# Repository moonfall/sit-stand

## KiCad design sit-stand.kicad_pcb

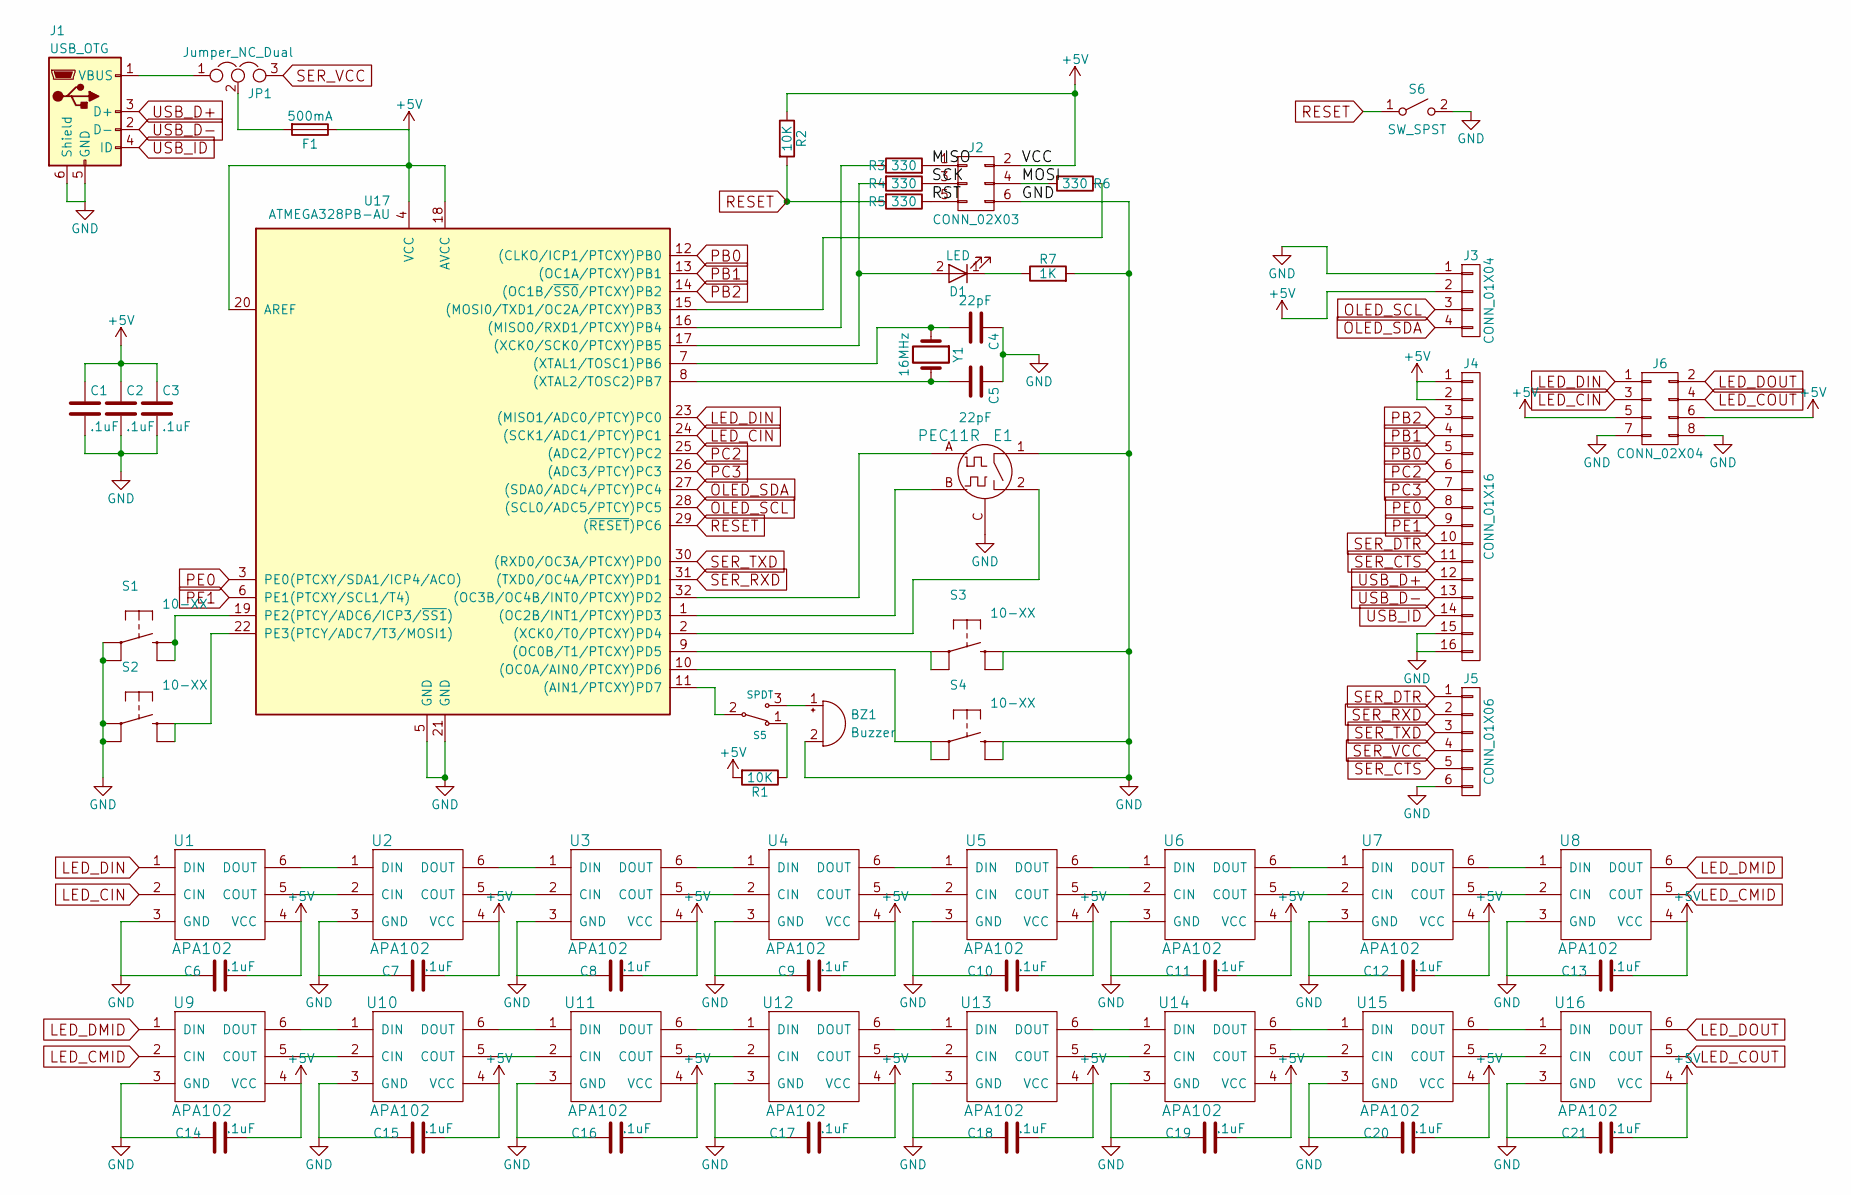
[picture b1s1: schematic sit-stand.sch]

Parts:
BZ1: Buzzer; BUZZER
C1, C2, C3, C6, C7, C8, C9, C10, C11, C12, C13, C14, C15, C16, C17, C18, C19, C20, C21: .1uF; C_0805_HandSoldering
C4, C5: 22pF; C_0805_HandSoldering
D1: LED; LED_0805
E1: PEC11R; pec11r
F1: 500mA; Fuse_SMD1206_HandSoldering
J1: USB_OTG; USB_Micro-B
J2: CONN_02X03; Pin_Header_Straight_2x03_Pitch2.54mm
J3: CONN_01X04; Pin_Header_Straight_1x04_Pitch2.54mm
J4: CONN_01X16; Pin_Header_Straight_1x16_Pitch2.54mm
J5: CONN_01X06; Pin_Header_Straight_1x06_Pitch2.54mm
J6: CONN_02X04; Pin_Header_Straight_2x04_Pitch2.54mm
JP1: Jumper_NC_Dual; Pin_Header_Straight_1x03_Pitch2.54mm
R1, R2: 10K; R_0805_HandSoldering
R3, R4, R5, R6: 330; R_0805_HandSoldering
R7: 1K; R_0805_HandSoldering
S1, S2, S3, S4: 10-XX; SW_TH_Tactile_Omron_B3F-10xx
S5: SPDT; SW_SPDT_CK-JS102011SAQN
S6: SW_SPST; SW_SPST_PTS645
U1, U2, U3, U4, U5, U6, U7, U8, U9, U10, U11, U12, U13, U14, U15, U16: APA102
U17: ATMEGA328PB-AU; TQFP-32_7x7mm_Pitch0.8mm
Y1: 16MHz; Crystal_HC49-U_Vertical

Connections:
+5V: C1.1, C2.1, C3.1, C6.2, C7.2, C8.2, C9.2, C10.2, C11.2, C12.2, C13.2, C14.2, C15.2, C16.2, C17.2, C18.2, C19.2, C20.2, C21.2, F1.1, J2.2, J3.2, J4.1, J4.2, J6.5, J6.6, R1.2, R2.1, U1.4 (VCC), U2.4 (VCC), U3.4 (VCC), U4.4 (VCC), U5.4 (VCC), U6.4 (VCC), U7.4 (VCC), U8.4 (VCC), U9.4 (VCC), U10.4 (VCC), U11.4 (VCC), U12.4 (VCC), U13.4 (VCC), U14.4 (VCC), U15.4 (VCC), U16.4 (VCC), U17.4 (VCC), U17.18 (AVCC), U17.20 (AREF)
/MISO: J2.1, R3.2
/MOSI: J2.4, R6.2
/RST: J2.5, R5.1
/SCK: J2.3, R4.1
GND: BZ1.2 (+), C1.2, C2.2, C3.2, C4.1, C5.1, C6.1, C7.1, C8.1, C9.1, C10.1, C11.1, C12.1, C13.1, C14.1, C15.1, C16.1, C17.1, C18.1, C19.1, C20.1, C21.1, E1.1, E1.C, J1.5 (GND), J1.6 (Shield), J2.6, J3.1, J4.15, J4.16, J5.6, J6.7, J6.8, R7.2, S1.3, S1.4 (P1), S2.3, S2.4 (P1), S3.1 (S), S3.2 (S1), S4.1 (S), S4.2 (S1), S6.2 (B), U1.3 (GND), U2.3 (GND), U3.3 (GND), U4.3 (GND), U5.3 (GND), U6.3 (GND), U7.3 (GND), U8.3 (GND), U9.3 (GND), U10.3 (GND), U11.3 (GND), U12.3 (GND), U13.3 (GND), U14.3 (GND), U15.3 (GND), U16.3 (GND), U17.5 (GND), U17.21 (GND)
LED_CIN: J6.3, U1.2 (CIN), U17.24 ((SCK1/ADC1/PTCY)PC1)
LED_CMID: U8.5 (COUT), U9.2 (CIN)
LED_COUT: J6.4, U16.5 (COUT)
LED_DIN: J6.1, U1.1 (DIN), U17.23 ((MISO1/ADC0/PTCY)PC0)
LED_DMID: U8.6 (DOUT), U9.1 (DIN)
LED_DOUT: J6.2, U16.6 (DOUT)
unnamed: BZ1.1 (-), S5.3
unnamed: C4.2, U17.7 ((XTAL1/TOSC1)PB6), Y1.1
unnamed: C5.2, U17.8 ((XTAL2/TOSC2)PB7), Y1.2
unnamed: D1.1 (K), R7.1
unnamed: D1.2 (A), R4.2, U17.17 ((XCK0/SCK0/PTCXY)PB5)
unnamed: E1.2, U17.2 ((XCK0/T0/PTCXY)PD4)
unnamed: E1.A, U17.32 ((OC3B/OC4B/INT0/PTCXY)PD2)
unnamed: E1.B, U17.1 ((OC2B/INT1/PTCXY)PD3)
unnamed: F1.2, JP1.2
unnamed: J1.1 (VBUS), JP1.1
unnamed: R1.1, S5.1
unnamed: R3.1, U17.16 ((MISO0/RXD1/PTCXY)PB4)
unnamed: R6.1, U17.15 ((MOSI0/TXD1/OC2A/PTCXY)PB3)
unnamed: S1.1 (S), S1.2 (S1), U17.19 (PE2(PTCY/ADC6/ICP3/~SS1~))
unnamed: S2.1 (S), S2.2 (S1), U17.22 (PE3(PTCY/ADC7/T3/MOSI1))
unnamed: S3.3, S3.4 (P1), U17.9 ((OC0B/T1/PTCXY)PD5)
unnamed: S4.3, S4.4 (P1), U17.10 ((OC0A/AIN0/PTCXY)PD6)
unnamed: S5.2, U17.11 ((AIN1/PTCXY)PD7)
unnamed: U1.5 (COUT), U2.2 (CIN)
unnamed: U1.6 (DOUT), U2.1 (DIN)
unnamed: U2.5 (COUT), U3.2 (CIN)
unnamed: U2.6 (DOUT), U3.1 (DIN)
unnamed: U3.5 (COUT), U4.2 (CIN)
unnamed: U3.6 (DOUT), U4.1 (DIN)
unnamed: U4.5 (COUT), U5.2 (CIN)
unnamed: U4.6 (DOUT), U5.1 (DIN)
unnamed: U5.5 (COUT), U6.2 (CIN)
unnamed: U5.6 (DOUT), U6.1 (DIN)
unnamed: U6.5 (COUT), U7.2 (CIN)
unnamed: U6.6 (DOUT), U7.1 (DIN)
unnamed: U7.5 (COUT), U8.2 (CIN)
unnamed: U7.6 (DOUT), U8.1 (DIN)
unnamed: U9.6 (DOUT), U10.1 (DIN)
unnamed: U9.5 (COUT), U10.2 (CIN)
unnamed: U10.5 (COUT), U11.2 (CIN)
unnamed: U10.6 (DOUT), U11.1 (DIN)
unnamed: U11.5 (COUT), U12.2 (CIN)
unnamed: U11.6 (DOUT), U12.1 (DIN)
unnamed: U12.5 (COUT), U13.2 (CIN)
unnamed: U12.6 (DOUT), U13.1 (DIN)
unnamed: U13.5 (COUT), U14.2 (CIN)
unnamed: U13.6 (DOUT), U14.1 (DIN)
unnamed: U14.5 (COUT), U15.2 (CIN)
unnamed: U14.6 (DOUT), U15.1 (DIN)
unnamed: U15.5 (COUT), U16.2 (CIN)
unnamed: U15.6 (DOUT), U16.1 (DIN)
OLED_SCL: J3.3, U17.28 ((SCL0/ADC5/PTCY)PC5)
OLED_SDA: J3.4, U17.27 ((SDA0/ADC4/PTCY)PC4)
PB0: J4.5, U17.12 ((CLKO/ICP1/PTCXY)PB0)
PB1: J4.4, U17.13 ((OC1A/PTCXY)PB1)
PB2: J4.3, U17.14 ((OC1B/~SS0~/PTCXY)PB2)
PC2: J4.6, U17.25 ((ADC2/PTCY)PC2)
PC3: J4.7, U17.26 ((ADC3/PTCY)PC3)
PE0: J4.8, U17.3 (PE0(PTCXY/SDA1/ICP4/ACO))
PE1: J4.9, U17.6 (PE1(PTCXY/SCL1/T4))
RESET: R2.2, R5.2, S6.1 (A), U17.29 ((~RESET~)PC6)
SER_CTS: J4.11, J5.5
SER_DTR: J4.10, J5.1
SER_RXD: J5.2, U17.31 ((TXD0/OC4A/PTCXY)PD1)
SER_TXD: J5.3, U17.30 ((RXD0/OC3A/PTCXY)PD0)
SER_VCC: J5.4, JP1.3
USB_D+: J1.3 (D+), J4.12
USB_D-: J1.2 (D-), J4.13
USB_ID: J1.4 (ID), J4.14

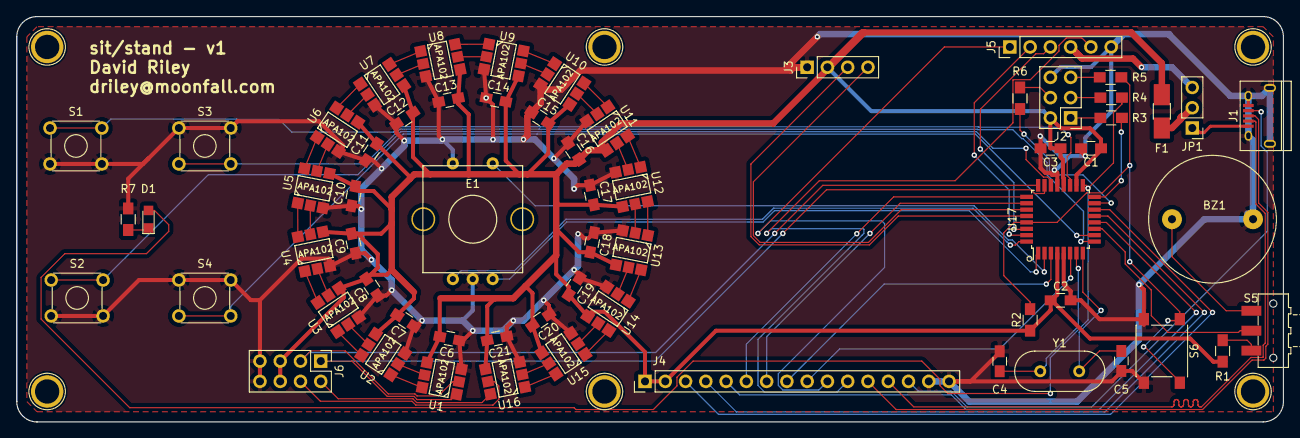
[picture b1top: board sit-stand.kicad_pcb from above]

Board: 2 copper layers, 158.8 x 50.8 mm, 63 parts (0 on the bottom side), 76 nets.

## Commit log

2017-06-11 Initial checkin.
2017-06-11 remove unused files
2017-06-11 clean up board
2017-06-11 shift oled and reroute led power
2017-06-11 use thicker led power traces
2017-06-11 added mounting holes
2017-06-11 fixed differentials
2017-06-11 fixed mounting holes positions
2017-06-11 add ground and power planes
2017-06-11 add text labels
2017-06-11 fix silkscreen
2017-06-11 update silk screen locations
2017-06-11 add pin 1 silk screen mark
